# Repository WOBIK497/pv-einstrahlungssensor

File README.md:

# PV-Einstrahlungssensor

Ein kabelloser Sensor, der die Sonneneinstrahlung **in der Ebene einer PV-Fläche** misst – auch dann, wenn der Wechselrichter abregelt. Ein kleines Solarmodul arbeitet als Messzelle, ein zweites versorgt die Elektronik über einen Superkondensator. Die Werte gehen per [BTHome](https://bthome.io) an Home Assistant, ganz ohne Akku, Batterie oder Kabel.

> **Stand: Entwurf (November 2026).** Platine, Gehäuse und Programm sind fertig konstruiert und rechnerisch geprüft, aber **noch nicht gebaut**. Was am ersten Exemplar zu prüfen ist, steht unter [Offene Punkte](#offene-punkte). Nachbau auf eigenes Risiko.

**English summary:** A wireless, battery-free irradiance sensor for balcony/rooftop PV. A 70 mm ETFE solar cell operated near short circuit across a 10 Ω shunt measures plane-of-array irradiance; a second cell charges a 4 F supercapacitor. An Espruino-powered Raytac MDBT42Q (nRF52832) broadcasts the readings as BTHome v2, received by Home Assistant via Shelly Bluetooth proxies. Includes a scripted KiCad 9 PCB (38 × 46 mm, JLCPCB-ready), a parametric FreeCAD enclosure (black ASA, O-ring sealed, membrane vent, printed tab that bolts to the panel frame flush with its front edge) and the Espruino program. A section compares other radio links (Wi-Fi, Zigbee, 868 MHz GFSK and LoRa) for larger rooftop arrays without a Bluetooth receiver nearby. Documentation is in German.

---

## Inhalt

- [Wozu?](#wozu)
- [Funktionsprinzip](#funktionsprinzip)
- [Überblick](#überblick)
- [Elektronik](#elektronik)
- [Platine](#platine)
- [Gehäuse](#gehäuse)
- [Programm (Espruino)](#programm-espruino)
- [Home Assistant](#home-assistant)
- [Abgleich](#abgleich)
- [Einkaufsliste](#einkaufsliste)
- [Aufbau und Montage](#aufbau-und-montage)
- [Offene Punkte](#offene-punkte)
- [Warum so und nicht anders](#warum-so-und-nicht-anders)
- [Andere Funkwege](#andere-funkwege)
- [Ordnerstruktur](#ordnerstruktur)
- [Lizenz](#lizenz)

---

## Wozu?

Eine PV-Anlage mit Speicher regelt ab, sobald der Akku voll ist und im Haus wenig verbraucht wird. Ab dann zeigt die Leistung des Wechselrichters nur noch, was abgenommen wird, und nicht mehr, was die Sonne hergeben würde. Damit fehlt die Grundlage für alles, was auf die **mögliche** Leistung reagieren soll: Überschussladen, Prognosen abgleichen, Verschattung oder Verschmutzung erkennen.

Der Sensor misst diese Größe direkt. Weil er in derselben Ebene wie das Paneel sitzt, sieht er dieselbe Einstrahlung, also Sonnenstand, Neigung, Ausrichtung und Wolken genauso wie das große Modul.

Für die eigene Anlage sind **drei** Sensoren vorgesehen, je einer pro Fläche:

| Sensor  | Paneele | Azimut | Neigung zur Waagerechten |
|---------|---------|--------|--------------------------|
| Süd     | 1 und 2 | 180°   | 55°                      |
| Südwest | 4       | 236°   | 65°                      |
| West    | 3       | 260°   | 65°                      |

Ein einziger Sensor und eine Umrechnung über die Geometrie hätten nicht genügt: Paneel 3 und 4 sind gleich steil, zeigen aber 24° auseinander, und das Verhältnis ihrer Erträge schwankte im Herbst zwischen 1,2 und 3,2.

## Funktionsprinzip

Eine Solarzelle liefert im Kurzschluss einen Strom, der sehr genau proportional zur Einstrahlung ist. Die Spannung hängt dagegen kaum davon ab. Der Sensor lässt das Messmodul deshalb fast im Kurzschluss auf einen 10-Ω-Widerstand (Shunt) arbeiten und misst die Spannung daran:

- 0,8-W-Modul, Kurzschlussstrom 143 mA bei 1.000 W/m²
- 143 mA × 10 Ω = **1,43 V bei 1.000 W/m²**, also rund **699 W/m² pro Volt**
- Selbst bei 1.300 W/m² (Sonne plus Reflexion von Wolkenrändern) sind es erst 1,86 V. Das ist ein Viertel der Leerlaufspannung, die Zelle bleibt im linearen Bereich (Abweichung < 0,5 %).

Ein zweites, baugleiches Modul lädt einen Superkondensator, aus dem das Funkmodul lebt. Messung und Versorgung sind getrennt, damit der Ladestrom die Messung nicht verfälscht.

## Überblick

| | |
|---|---|
| Messgröße | Einstrahlung in der Modulebene, W/m² |
| Messzelle | ETFE-Solarmodul 70 × 70 mm, 0,8 W, auf 10-Ω-Shunt |
| Versorgung | zweites Modul → 5-V-Regler → Superkondensator 5,5 V / 4 F → 3,3 V |
| Funk | BTHome v2 (Bluetooth LE Advertising), unverschlüsselt |
| Funkmodul | Raytac MDBT42Q-512KV2 (nRF52832), Espruino selbst per SWD aufgespielt |
| Takt | messen alle 3 s, senden jede Sekunde |
| Verbrauch | ≈ 40 µA im Mittel, Kondensator überbrückt ≈ 2 Tage Dunkelheit |
| Kaltstart | ≈ 6 min bei bedecktem Himmel (200 W/m²) |
| Platine | 38 × 46 mm, 2 Lagen, SMD-Bestückung durch JLCPCB |
| Gehäuse | 3D-Druck (ASA, schwarz), 160 × 90 × 32,2 mm, O-Ring-gedichtet, Druckausgleichselement, angedruckte Lasche für den Paneelrahmen |
| Kosten | rund 90 € für einen Sensor, jeder weitere rund 50 € |

## Elektronik

```
VERSORGUNG
  Modul V (J1) ─ R2 10 Ω ─ U1 HT7550 (5,0 V) ─ D1 B5819WS ─┬─ VCAP ≤ 4,8 V ── J3: Superkondensator 4 F / 5,5 V
                C1 10 µF        C2 10 µF                 │   C3, C4 2 × 22 µF
                                                         ├─ R4 1 MΩ ─┬─ R5 1 MΩ ─ GND
                                                         │           └─ DIV → P0.30 (D30), C9 100 nF
                                                         └─ U2 XC6206 (3,3 V) ─ 3V3 → MDBT42Q
                                                               C6 10 µF, C7 100 nF
MESSUNG
  Modul M (J2) ─┬─ R1 10 Ω, 2 W (Shunt) ─ GND
                └─ R3 10 kΩ ─ SENSE 0 … 1,9 V → P0.31 (D31), C8 100 nF

MDBT42Q (U3):  P0.00 (D0) Taster-Ersatz J5 · P0.01 (D1) LED D2 über R6 1 kΩ
               RX mit R7 1 MΩ nach GND · SWD, RX, TX auf J4
```

- **R2** vor dem 5-V-Regler nimmt dem kleinen SOT-23-Gehäuse bei vollem Ladestrom die Wärme ab (sonst bis zu 0,2 W im Regler).
- **D1** verhindert, dass sich der Kondensator nachts über Regler und Modul entlädt.
- **R4/R5** teilen die Kondensatorspannung durch zwei (Querstrom 2,4 µA).
- **R7** hält RX auf Masse, damit Espruino beim Start nicht versehentlich die serielle Konsole statt Bluetooth wählt.
- Taster und LED liegen wie auf dem offiziellen Espruino-Breakout an D0 und D1, Programme und Anleitungen dafür passen also unverändert.
- Ruhestrom beider Regler zusammen ≈ 3 µA (HT7550 1,5 µA, XC6206 1 µA).

**Anschlüsse** (eckiges Pad = Pin 1, bei J1–J3 also Plus):

| | Belegung | Wofür |
|---|---|---|
| J1 | + / −, ZH-Buchse 1,5 mm | Modul V (Versorgung), Stecker des Moduls direkt |
| J2 | + / −, ZH-Buchse 1,5 mm | Modul M (Messung), Stecker des Moduls direkt |
| J3 | + / −, ZH-Buchse 1,5 mm | Superkondensator über ein konfektioniertes ZH-Kabel |
| J4 | GND, 3V3, SWDIO, SWDCLK, RX, TX | Espruino aufspielen (SWD); im Notfall serielle Konsole |
| J5 | D0 / 3V3 | Taster-Ersatz: beim Einschalten überbrücken, um gespeicherten Code zu umgehen |

J4 und J5 sind Lötaugen im Raster 2,54 mm.

## Platine

| Oberseite | Unterseite |
|---|---|
|  |  |

Zwei Lagen, 38 × 46 mm, alle Bauteile oben. Die Antenne des Funkmoduls sitzt an der Oberkante, darunter bleibt ein 4 mm breiter Streifen auf beiden Lagen kupferfrei. Links die Messung, unten die Versorgung, rechts die Programmierleiste. Die Unterseite ist eine durchgehende Massefläche. Die Entwurfsregelprüfung (DRC) von KiCad meldet **0 Fehler und 0 offene Verbindungen** (`drc.json`).

Die Platine wird vollständig per Skript erzeugt. Es gibt keinen Schaltplan in KiCad, die Netze stehen in `erzeuge_platine.py`.

```bash
cd Einstrahlungssensor-Platine
./erzeuge_fertigung.sh     # baut die Platine, DRC, Gerber-ZIP, BOM/CPL, Renderings
```

Voraussetzung: KiCad 9 mit Python-Modul `pcbnew` und `kicad-cli` (getestet mit 9.0.8 unter Kubuntu).

> Falle beim Skripten: Der Zonen-Füller stürzt auf einem frisch erzeugten `BOARD` ab. Das Skript speichert deshalb erst, lädt neu und füllt dann.

### Bestellen bei JLCPCB

1. `einstrahlungssensor-gerber.zip` hochladen. Die Vorgaben passen: 2 Lagen, 1,6 mm. Als Oberfläche **LeadFree HASL** statt OSP wählen, weil Funkmodul und Buchsen nach dem Reflow noch von Hand gelötet werden.
2. „PCB Assembly“ einschalten: Economic, Seite „Top“, bis zu 5 Platinen bestücken, **Confirm Parts Placement = Yes**.
3. `jlcpcb-bom.csv` und `jlcpcb-cpl.csv` hochladen (11 Positionen). Alle Teile haben LCSC-Nummern. J1–J5 und das Funkmodul fehlen mit Absicht.
4. **In der Bestückungsvorschau prüfen:** Polung von D1 (Kathodenstrich zu J3/C3) und D2, Lage von U1 (Pin 1 links oben) und U2 (Pin 1 rechts unten). JLCPCB dreht manche Bauteile anders als KiCad; die CPL enthält dafür schon eine Drehkorrektur. Nach der Bestellung die Platzierung binnen 72 Stunden freigeben.
5. Die ZH-Buchsen J1–J3 sind Durchsteckteile und stehen nicht in der Stückliste. Du lötest sie selbst ein und kaufst sie getrennt: JLCPCB verschickt keine losen Teile, was dort zusätzlich gekauft wird, bleibt im Teilelager für spätere Bestückungen.

Bei der Bestellung (November 2026) fielen außerdem auf: JLCPCB setzt mit der Voreinstellung „Tooling holes: Added by JLCPCB“ zwei Werkzeuglöcher (Ø 1,15 mm, nicht durchkontaktiert) in die oberen Ecken. Sie liegen im kupferfreien Antennenstreifen und außerhalb der Schlitzhalter im Gehäuse und stören nicht. In die EU zieht der Versand „Global Standard Direct Line“ Einfuhrumsatzsteuer, EU-Zoll und EU-Bearbeitungsgebühr gleich mit ein; bei den Express-Diensten unter IOSS kommen Zoll und Gebühr erst bei der Zustellung dazu.

| Bauteil | LCSC | Hinweis |
|---|---|---|
| HT7550-1 (MSKSEMI), 5-V-Regler | C5379082 | Pin 1 GND, 2 VIN, 3 VOUT |
| XC6206P332MR, 3,3-V-Regler | C5446 | Pin 1 GND, 2 VOUT, 3 VIN (anders als der HT7550!) |
| 10 Ω, 1 %, 2 W, 2512 (R1, R2) | C414890 | |
| B5819WS Schottky (D1) | C7420331 | |
| ZH-Buchse 2-polig, stehend (J1–J3) | – | Bauform JST B2B-ZR, nicht in der Stückliste: getrennt kaufen und selbst einlöten |
| übrige R, C und LED | siehe BOM | Standardteile |

### Funkmodul und Buchsen auflöten

Die drei ZH-Buchsen J1–J3 von oben einstecken und von unten verlöten, das eckige Pad (Pin 1, Plus) beachten. Sie sind unkritisch, am besten nach dem Funkmodul, damit sie beim Löten des Moduls nicht im Weg sind.

Das MDBT42Q lötest du ebenfalls selbst auf (Pads im Abstand von 0,7 mm an der Kante):

1. Viel Flussmittel, feine Spitze, Entlötlitze für Brücken.
2. Eine Ecke heften, Lage prüfen, dann die gegenüberliegende Ecke, dann den Rest.
3. Antenne zur Oberkante, Pad 1 (Markierung) oben links.
4. Vor dem ersten Einschalten mit dem Multimeter prüfen, dass 3V3 und GND an J4 nicht kurzgeschlossen sind.

Ohne Lötkolben geht es auch mit einer **Heizplatte** und Niedertemperatur-Lötpaste (Sn42Bi58, schmilzt bei 138 °C): Paste mit der Nadel auf die Pads, Modul auflegen, Platte auf etwa 170–180 °C. Die Lötstellen der JLCPCB-Bestückung (bleifrei, 217 °C) schmelzen dabei nicht, nichts verrutscht. Vorher einen Probelauf mit etwas Paste machen, weil die Anzeige der Platte mehr zeigt, als oben auf der Platine ankommt. Erst danach die ZH-Buchsen und J4 mit dem Lötkolben einlöten, die Buchsengehäuse nicht mit auf die Platte. Wismut-Lot ist etwas spröder als normales; für ein Modul mit vielen Pads im geschlossenen Gehäuse ist das vertretbar.

## Gehäuse

| Unterteil | Boden |
|---|---|
|  |  |

Zwei Druckteile, beide passen auf ein 180-mm-Druckbett. Für ASA braucht der Drucker einen geschlossenen Bauraum (z. B. Prusa Core One):

- **Außenmaß** 160 × 90 × 32,2 mm (Unterteil 25,0 mm, Deckel 7,2 mm), mit Lasche 160 × 118 mm. Innenraum 149,6 × 79,6 × 22,6 mm.
- **Deckel:** eine gemeinsame Tasche (143,4 × 72,2 × 2,8 mm) für beide Module. Die Module liegen auf einer 1 mm dicken Klebefuge und schließen **bündig** mit der Deckeloberseite ab. Abstandsnoppen auf dem Klebering (vier je Modul) legen die Fugendicke fest, Positionsnoppen an den Taschenwänden die Lage, zwei Distanznoppen halten 1 mm Abstand zwischen den Modulen. Unter jedem Modul ein Fenster für Kabel und Anschlussdose. Obere Außenkante mit R 2 abgerundet, außer zur Rahmenseite.
- **Dichtung:** geschlossener **O-Ring 148 × 2 mm, EPDM 70** (wetter-, UV- und ozonfest) als Axialdichtung in einer Nut von 2,8 × 1,5 mm (≈ 25 % Verpressung, 75 % Nutfüllung, 1,9 % Dehnung). Passend sind O-Ringe mit 146–150 mm Innendurchmesser.
- **Verschraubung:** acht Senkschrauben **M3 × 30** von unten durch Dome im Unterteil in Gewindeeinsätze M3 × 5,7 im Deckel (5 mm Gewindeeingriff). Die Nut läuft innen um die Dome herum, die Schraubenlöcher liegen also außerhalb der Dichtung.
- **Druckausgleich:** ein Membranelement **M12 × 1,5** sitzt versenkt in einer Tasche im Boden (Sechskant gegen Mitdrehen), innen mit einer Gegenmutter gekontert. Es lässt Luft durch, aber kein Wasser, und verhindert, dass das Gehäuse bei Temperaturwechseln Feuchtigkeit ansaugt.
- **Platine:** Die Antennenkante steckt in zwei Haltern mit Schlitz, die Unterkante liegt auf zwei Abstandshaltern (5 mm) und wird mit zwei Linsenkopfschrauben M3 × 6 (ISO 7045) befestigt, die sich ihr Gewinde im 2,6-mm-Loch selbst formen.
- **Superkondensator:** liegt zwischen zwei Stirnanschlägen (an der Drahtseite niedrig, die Drähte laufen darüber) und wird in zwei Schnappklammern gedrückt (federnde Arme 1,0 mm dick, Rastnase 25° über dem Zellenäquator, 1,1 % Dehnung beim Einrasten – ASA ist spröder als PETG und quer zu den Lagen schwächer, darum unter 2 %).
- **Befestigung:** Die Halterung ist für **quer oder hochkant verbaute Paneele** gedacht. Bei quer verbauten (lange Seite waagerecht) liegen die Montagelöcher in den Rahmenseiten oben und unten, der beste Platz für den Sensor ist **oben**: Dort sieht er denselben Himmel wie das Paneel, wird nicht von Brüstung, Geländer oder einer unteren Paneelreihe verschattet, und Regenwasser, Schnee und Schmutz laufen vom Paneel nach unten ab statt über den Sensor. Bei hochkant verbauten sitzt der Sensor seitlich an einer Langkante, am besten am oberen Montageloch. Das Gehäuse sitzt neben der oberen Langkante des Paneels und liegt mit der Wand direkt am Rahmen an. Eine Lasche (160 × 28 × 2,2 mm), in einem Stück mit dem Unterteil gedruckt, greift hinten unter den Fußflansch des Rahmens und wird mit **einer M6-Schraube durch ein Montageloch im Rahmenflansch** gehalten (Langloch ±2 mm). Gemeint sind die Montagelöcher, die gerahmte PV-Paneele ab Werk im Fußflansch der langen Rahmenseiten haben und die im Datenblatt des Paneels eingezeichnet sind. Gebohrt wird nichts. So liegt der Deckel **bündig mit der Rahmenvorderkante**: Das Gehäuse verschattet das Paneel nicht und der Rahmen nicht die Module. Die Wand am Rahmen verhindert das Verdrehen und trägt das Gewicht. Zur Rahmenseite haben Unterteil und Deckel keine Eckradien, damit sich kein Schmutz in Zwickeln sammelt. Die Lasche ist nur 2,2 mm dick, weil sie genau den Höhenunterschied zwischen Gehäuse (32,2 mm) und Rahmen (30 mm) ausfüllt. Sie hält trotzdem rund 270 N senkrecht zum Paneel (ASA, vorsichtig mit 40 MPa gerechnet), eine Sturmböe drückt mit 15–20 N. Rahmenmaße nach dem Datenblatt JA Solar JAM60D41 (langer Rahmen 30 mm hoch, Fußflansch 28 mm, Lochmitte 19 mm von der Außenfläche): Bei anderen Paneelen die Parameter `RAHMEN_*` und `MONTAGELOCH_ABSTAND` im Skript anpassen.

| Montiert, von vorn | Montiert, von hinten |
|---|---|
|  |  |

Alle Maße stehen als Parameter oben in `erzeuge_gehaeuse.py`. Neu erzeugen (FreeCAD 1.x, headless):

```bash
cd Einstrahlungssensor-Gehäuse
freecad.cmd erzeuge_gehaeuse.py     # → gehaeuse-unterteil/-deckel als STL und STEP
freecad.cmd pruefe_gehaeuse.py      # Passungsprüfung: Platine, Stecker, Kondensator, Druckausgleich
python3 vorschau.py                 # Vorschaubilder in Bilder/ (nur Pillow nötig)
```

Das Skript gibt beim Bauen die wichtigsten Kontrollmaße aus: Gewindeeingriff, Wandstärken an Einsätzen und Senkungen, Nutfüllung, O-Ring-Dehnung, Federweg der Schnappklammern. `pruefe_gehaeuse.py` meldet für den aktuellen Stand **0 Überschneidungen**.

`live_ansicht.py`, `live_uebernehmen.sh` und `live_befehl.sh` sind ein Hilfsmittel zum gemeinsamen Konstruieren: Das Makro läuft in der FreeCAD-Oberfläche, baut das Modell neu, sobald sich das Skript ändert, und zeigt Platine, Kabel, Schrauben und Module mit. Die Texturen dafür liegen im Ordner `Live-Ansicht/`, der nicht im Repository ist. Die Moduloberfläche erzeugt `erzeuge_modultextur.py`, die Platinenbilder kommen von `platine_ansicht_daten.py`. Für den Nachbau braucht man das alles nicht.

Zum Anschauen gibt es die Baugruppe als FreeCAD-Datei: `Gehäuse mit Einbauteilen offen.FCStd` und `… geschlossen.FCStd` zeigen das Gehäuse mit allen Einbauteilen am Paneelrahmen; `Gehäuse mit Einbauteilen.FCStd` ist ein älterer Stand ohne Lasche und Gewindeeinsätze. In „offen“ und „geschlossen“ sind die Bilder von Solarmodulen, Platine, Funkmodul und Druckausgleich eingebettet. FreeCAD 1.1 zeichnet Bilder auf Part-Objekten aber nicht selbst, darum legt das Hilfsobjekt `Texturen` sie beim Öffnen auf. Dafür muss `pv_textur.py` für FreeCAD importierbar sein, z. B. als Verknüpfung in einem Unterordner von `Mod/` in den FreeCAD-Benutzerdaten (den Pfad nennt `App.getUserAppDataDir()`, beim Snap `~/snap/freecad/common/`). Ohne das Modul öffnen sich die Dateien trotzdem, die Bildflächen bleiben dann grau.

### Drucken

- **Material: ASA, schwarz.** Die beiden schwarzen Solarzellen im Deckel heizen sich in der Sommersonne auf 65–70 °C auf, und das Gehäuse liegt direkt am Rahmen des PV-Paneels, der ebenso heiß wird. PETG wird ab etwa 70 °C weich und gäbe unter der Dauerlast (O-Ring-Pressung durch acht Schrauben, gespannte Lasche) über die Jahre nach; ASA hält bis etwa 95 °C und ist dazu UV-beständig. Schwarz, weil Ruß als Pigment am wenigsten ausbleicht und zusätzlich UV abfängt; ein heller Kunststoff kühlt kaum, denn die Wärme kommt vor allem von den Modulen im Deckel. Kein PLA (weich ab etwa 55 °C). PETG geht auf einem offenen Drucker zur Not auch, hält aber weniger lange.
- **Drucker:** ASA nur mit geschlossenem Bauraum, auf einem offenen Drucker verzieht sich das 16 cm lange Unterteil. Brim am Unterteil, Bauraum vorheizen, Raum lüften (Styrol).
- **Lage:** Unterteil mit dem Boden aufs Bett, die Lasche liegt mit auf. Deckel mit der Tasche nach oben. Kein Stützmaterial. Die Klammerarme stehen senkrecht, ihre Biegung geht quer zu den Lagen – nicht anders drucken, aber auch nicht beim Einsetzen des Kondensators hebeln.
- **Einstellungen:** 0,2 mm Schichthöhe, 4 Perimeter, 5 obere und untere Schichten, 25 % Gyroid. Die vielen Perimeter machen die Wände dicht.
- **Gewindeeinsätze:** Löcher 4,0 mm für M3 × 5,7 im Deckel, passend etwa zu Ruthex. Andere Einsätze → Maße im Skript anpassen.

## Programm (Espruino)

[`Firmware/einstrahlung-sued.js`](Firmware/einstrahlung-sued.js) misst alle 3 Sekunden beide Spannungen (16-fach gemittelt) und sendet sie jede Sekunde als BTHome-Advertising:

| BTHome-Objekt | Wert | Auflösung |
|---|---|---|
| `0x0C` voltage | Spannung am Shunt | 1 mV ≙ 0,7 W/m² |
| `0x4A` voltage | Spannung am Superkondensator | 0,1 V |

Espruino misst relativ zur Betriebsspannung. Das Programm rechnet deshalb mit `E.getAnalogVRef()` in Volt zurück. Für die anderen Sensoren änderst du nur `NAME` in der ersten Zeile.

**Espruino einmalig aufspielen.** Das nackte MDBT42Q kommt vom Distributor ohne Firmware. Espruino kommt deshalb einmal per SWD über J4 darauf, als Programmer dient ein Raspberry Pi Pico mit der Firmware [debugprobe](https://github.com/raspberrypi/debugprobe) (UF2-Datei per Drag-and-drop):

1. Verdrahtung Pico → J4: GP2 → SWDCLK, GP3 → SWDIO, GND → GND. Solange der Superkondensator noch nicht eingesteckt ist, darf der Pico die Platine über 3V3 versorgen. Mit eingestecktem, geladenem Kondensator 3V3 **nicht** verbinden, sonst fließt Strom rückwärts durch den XC6206.
2. Neue nRF52 sind oft per APPROTECT gesperrt. Erst entsperren (löscht den Chip):
   `openocd -f interface/cmsis-dap.cfg -f target/nrf52.cfg -c "init; nrf52_recover; exit"`
3. Die `.hex`-Datei für das MDBT42Q von [espruino.com/Download](https://www.espruino.com/Download) aufspielen:
   `openocd -f interface/cmsis-dap.cfg -f target/nrf52.cfg -c "program <datei>.hex verify reset exit"`

Ein ST-Link reicht dafür nicht: Er kann einen gesperrten nRF52 nicht entsperren. Der Pico bringt mit debugprobe außerdem eine serielle Schnittstelle mit (GP4 → RX, GP5 ← TX an J4), für die Espruino-Konsole mit 9600 Bd. Wer Espruino auf fremder Hardware nutzt, freut sich das Projekt über eine Spende.

**Programm aufspielen** (per Bluetooth, auch wenn der Sensor schon montiert ist):

1. Die [Espruino Web IDE](https://www.espruino.com/ide/) in Chrome öffnen. Unter Linux vorher in `chrome://flags` die „Experimental Web Platform Features“ einschalten. Von Android geht es ohne diesen Schritt.
2. Kondensator laden lassen (oder kurz 3,3 V an J4 anlegen), mit dem Modul verbinden, Programm einfügen und hochladen.
3. In der Konsole `save()` eingeben. Danach startet das Programm nach jedem Stromausfall von selbst.

**Absichern:** Solange das Modul verbindbar ist, kann sich jeder in Funkreichweite mit der Web IDE verbinden. Mit `E.setPassword("…")` und `E.lockConsole()` lässt sich die Konsole sperren. Passwort vergessen: J5 beim Einschalten etwa 5 Sekunden überbrücken, dann startet das Modul ohne gespeichertes Programm.

## Home Assistant

Die **BTHome-Integration** erkennt den Sensor von selbst, sobald ein Bluetooth-Empfänger ihn hört (hier: Shelly-Geräte als Bluetooth-Proxy). Weil die Bibliothek die Werte nach Objektnummer sortiert, kommt die Shunt-Spannung zuerst. Die Entitäten heißen voraussichtlich „Spannung“ und „Spannung 2“.

Für die Einstrahlung einen **Template-Sensor** anlegen (Helfer → Template → Sensor):

- Einheit `W/m²`, Geräteklasse „Bestrahlungsstärke“ (`irradiance`), Zustandsklasse „Messung“
- Zustand:

```jinja
{{ (states('sensor.einstr_sued_spannung') | float(0) * 699) | round(0) }}
```

Die Entitäts-ID durch die tatsächliche ersetzen, den Faktor 699 nach dem [Abgleich](#abgleich) durch den gemessenen.

**Recorder entlasten:** Die Shunt-Spannung ändert sich fast bei jeder Messung. Ein Sensor im 3-Sekunden-Takt erzeugt zusammen mit seinem W/m²-Sensor knapp 60.000 Zustände am Tag. Die rohen Spannungen deshalb vom Recorder ausschließen und nur die W/m²-Werte speichern:

```yaml
recorder:
  exclude:
    entity_globs:
      - sensor.einstr_*_spannung*
```

## Abgleich

Der Faktor 699 ist der Nennwert aus dem Datenblatt. Für den echten Wert an Tagen ohne Abregelung die Shunt-Spannung gegen die Leistung der zugehörigen Strings aufzeichnen und aus **5-Minuten-Mittelwerten bei klarem Himmel** den Faktor je Fläche bestimmen. Die Mittelung gleicht auch den Versatz von ein, zwei Sekunden zwischen Sensor und Wechselrichter aus. Bei mehreren Sensoren müssen diese untereinander nicht synchron senden, weil jeder nur mit seinen eigenen Strings verglichen wird.

Bei mehreren Sensoren sollten die **Messmodule aus derselben Charge** stammen, damit alle gleich messen. Bei den Versorgungsmodulen ist das egal.

## Einkaufsliste

Für einen Sensor, Preise vom November 2026 inklusive Mehrwertsteuer, ohne Versand:

| Teil | Menge | ca. Preis | Bezug |
|---|---|---|---|
| Funkmodul Raytac MDBT42Q-512KV2 (nRF52832, 512 KB, Keramikantenne), ohne Firmware | 1 | ≈ 6 € | z. B. [TME](https://www.tme.eu/de/details/mdbt42q-512kv2/iot-wifi-bluetooth-modules/raytac/); nicht das MDBT42Q-PAT (nRF52810, kein Espruino). Der Espruino-Shop hatte das nackte Modul im November 2026 nicht mehr, nur das Breakout, das nicht auf die Platine passt |
| Raspberry Pi Pico (H) als SWD-Programmer, einmalig für alle Sensoren | 1 | ≈ 5–10 € | |
| Leiterplatten, bestückt (JLCPCB fertigt mindestens 5) | 5 | ≈ 23 $ für alle fünf bestückt, mit Versand und Einfuhrabgaben nach Deutschland und Neukunden-Gutschein (November 2026) | JLCPCB |
| ZH-1,5-Set: 2-polige Stecker mit Kabel und stehende Platinenbuchsen (Buchsen für J1–J3, ein Kabel für J3) | 1 Packung | ≈ 8 € | z. B. Amazon (Nachbau, Passung zu den Modulsteckern prüfen) |
| ETFE-Solarmodul 0,8 W, 6 V, 70 × 70 × 2 mm, ZH-1,5-Stecker (1 × Messung, 1 × Versorgung) | 2 | 17–32 € | AliExpress |
| Superkondensator 5,5 V / 4 F (Kombityp, zwei Zellen) | 1 | 3,50 € | AliExpress |
| Druckausgleichselement M12 × 1,5, PA, PTFE-Membran, IP68 (z. B. Jacob JDAE12) | 1 | 3,25 € | Fachhandel |
| O-Ring 148 × 2 mm, EPDM 70 | 1 | 4 € | Fachhandel |
| Gewindeeinsätze M3 × 5,7 | 8 | | z. B. Ruthex |
| Befestigung: Sechskantschraube M6 × 16 (ISO 4017), Karosseriescheibe 6,4 × 18, Sicherungsmutter M6 (DIN 985), Edelstahl | je 1 | | |
| Senkschrauben M3 × 30 (ISO 10642), Edelstahl | 8 | | |
| Linsenkopfschrauben M3 × 6 (ISO 7045), Edelstahl, für die Platine | 2 | | |
| Mutter M12 × 1,5 (Kunststoff), falls beim Druckausgleich keine dabei ist | 1 | | |
| ASA, schwarz | ≈ 100 g | | |

Wer mehrere Sensoren baut, braucht alles außer den Leiterplatten und dem ZH-Set entsprechend öfter. Pro weiterem Sensor kommen so rund 50 € dazu. Die Messmodule sollten dann aus derselben Charge stammen (siehe [Abgleich](#abgleich)).

Dazu aus der Bastelkiste: Lötzinn, Flussmittel, Entlötlitze, Schrumpfschlauch, wetterfester Kleb- und Dichtstoff auf MS-Polymer-Basis für die Module. Eine 6-polige Stiftleiste für J4 (zum Aufspielen von Espruino) und ein paar Jumperkabel Buchse–Buchse.

## Aufbau und Montage

1. Funkmodul und die drei Buchsen auf die bestückte Platine löten und auf Kurzschluss prüfen (siehe [oben](#funkmodul-und-buchsen-auflöten)).
2. Gewindeeinsätze einschmelzen: acht M3 von unten in den Deckel.
3. Druckausgleichselement von außen in die Bodentasche setzen und innen mit der Mutter kontern.
4. Dichtstoff auf den Klebering geben, die Kabel der Solarmodule durch die Fenster im Deckel fädeln und die Module in die Tasche drücken, bis sie auf den Abstandsnoppen aufliegen und zwischen den Positionsnoppen sitzen. Das Messmodul markieren.
5. Die Fugen um die Module umlaufend mit dem Kleber versiegeln. Die Module sind auf FR-4 laminiert, die offene Kante ist die Schwachstelle.
6. **Polung der Modulstecker prüfen:** Rot (Plus) muss auf die Seite mit dem „+“ auf der Platine. Falls nicht, lassen sich die Kontakte aus dem ZH-Gehäuse lösen und tauschen (Lasche mit einer Nadel anheben). Verpolt geht nichts kaputt, der Sensor misst und lädt dann nur nicht.
7. Messmodul in J2, Versorgungsmodul in J1. Ein ZH-Kabel an den Superkondensator löten (Rot an Plus, Schrumpfschlauch) und in J3 stecken. Alternativ den Kondensator direkt auf die Platine löten: J3 dann nicht bestücken und die Kondensatordrähte, falls nötig mit zwei Litzen verlängert, in die Lötaugen von J3 löten, Plus ans eckige Pad. Der Kondensator lässt sich dann allerdings nicht mehr abziehen.
8. Platine mit der Antennenkante schräg in die Schlitze schieben, ablegen, unten mit zwei M3 × 6 festschrauben. Kondensator in die Klammern drücken.
9. O-Ring in die Nut legen, Deckel aufsetzen und mit acht M3 × 30 von unten gleichmäßig anziehen, bis er rundum aufliegt.
10. Den Sensor an die obere Langkante des quer verbauten Paneels setzen (bei hochkant verbauten seitlich ans obere Montageloch): Wand am Rahmen, Lasche hinten am Fußflansch, Langloch über dem Montageloch im Rahmenflansch. Die M6 × 16 von innen durch den Flansch stecken (Kopf zwischen Flansch und Paneel), hinten Karosseriescheibe und Sicherungsmutter, nur mäßig anziehen – auch ASA gibt unter zu viel Druck auf Dauer nach. Nicht in den Rahmen bohren.

## Offene Punkte

Folgendes ist bisher nur aus Datenblättern und Quelltext abgeleitet. Deshalb zuerst **ein** Exemplar bauen und in Betrieb nehmen:

- **Bestückung:** Sitzen D1 und D2 richtig herum? Höchstens 4,9 V am Kondensator, 3,3 V an J4?
- **Stecker:** Passen die Modulstecker in die ZH-Buchsen, und auf welcher Seite liegt Rot?
- **Gehäuse:** Module (70,2 × 70,2 × 1,8 mm) und Kondensator (22,8 × 25,6 × 13,0 mm) sind nachgemessen und eingetragen, ebenso das Druckausgleichselement (Sechskantkopf SW 16,8 × 8,2 mm, Gewinde 10 mm, Belüftungsschlitze in der Kopfmitte frei vom 3 mm tiefen Sechskantsitz). Gegenmutter gemessen (5,1 mm hoch), der O-Ring des Elements liegt in einer Nut im Kopf. Der Grund dieser Tasche wird als Brücke gedruckt: Liegt der Dichtring des Elements dort sauber an? Bleibt das Gehäuse unter der Brause dicht?
- **Befestigung:** Passt das Paneel zum Datenblatt JAM60D41 (Rahmen 30 mm hoch, Flansch 28 mm), trifft das Langloch das Montageloch, liegt der Deckel bündig? Die Flanschdicke ist aus der maßstabsgetreuen Profilzeichnung im Datenblatt ausgemessen (≈ 1,7 mm), M6 × 16 reicht bis etwa 4 mm.
- **Empfang:** Hört ein Bluetooth-Proxy den Sensor am Montageort zuverlässig?
- **Nacht:** Wie weit sinkt die Kondensatorspannung bis zum Morgen (Leckstrom)?
- **Web Bluetooth:** Klappt die Verbindung vom Linux-Rechner oder nur vom Android-Gerät?
- **Home Assistant:** Welche Spannung landet unter welcher Entität?
- **Abgleich:** Faktor je Fläche aus Messungen bestimmen.

## Warum so und nicht anders

- **Espruino statt ESPHome:** ESPHome kann BTHome nur empfangen, nicht senden. Der Vorschlag, das Senden einzubauen ([esphome/esphome#14472](https://github.com/esphome/esphome/pull/14472)), wurde im Oktober 2026 ohne Übernahme geschlossen. Espruino bringt eine fertige [BTHome-Bibliothek](https://www.espruino.com/BTHome) mit, das Programm ist ein paar Zeilen JavaScript und lässt sich per Bluetooth ändern.
- **Eigene Platine statt Breakout auf Lochraster:** kleiner, robuster und kaum teurer, weil JLCPCB alles außer dem Funkmodul und den Buchsen bestückt.
- **Superkondensator statt Akku:** keine Alterung durch Ladezyklen, kein Problem mit Frost oder Hitze unter dem Modul.
- **Variante mit externer Stromversorgung:** Liegt am Montageort Strom an, wäre nur ein Modul nötig, nämlich das Messmodul. Versorgungsmodul, 5-V-Regler und Superkondensator entfallen, und das Gehäuse wäre nur halb so groß. Dadurch wäre auch WLAN (z. B. mit ESPHome) oder Zigbee2MQTT möglich, weil der höhere Stromverbrauch dann keine Rolle spielt (siehe [Andere Funkwege](#andere-funkwege)).
- **Verworfen:** Lux-Sensoren (enden bei etwa 83.000 lx und messen Lux statt W/m²), Industrie-Einstrahlungssensoren (450–700 € pro Stück). Ein Silizium-Pyranometer mit RS485 (z. B. PYR20, ca. 60 €) wäre die fertige Alternative, braucht aber Kabel. Fertige BTHome-Geräte mit freiem Analogeingang gibt es meines Wissens nicht.

## Andere Funkwege

Dieser Sensor bleibt bei Bluetooth LE, weil am Balkon Shelly-Geräte als Empfänger in Reichweite sind. Bei größeren Dachanlagen ist das oft nicht so. Die Übersicht ist für alle, die den Sensor dafür abwandeln wollen. Alle Zahlen sind Überschläge aus Datenblättern, gemessen ist davon nichts.

**Maßstab ist die Solarversorgung:** Das Versorgungsmodul liefert rund 0,14 mA je W/m², der Superkondensator gibt zwischen 4,7 und 2,0 V etwa 11 C ab. Damit er eine Winternacht von 15 Stunden überbrückt, darf der Sensor im Mittel höchstens etwa **0,2 mA** brauchen. Die Ströme unten beziehen sich auf den Kondensator. Der 3,3-V-Regler ist linear, es fließt also derselbe Strom hinein wie heraus.

**Reichweite und Verbrauch**

| Funkweg | Reichweite bei Sicht | Reichweite durchs Haus | Mittlerer Strom, ein Wert alle 3 s | Reicht die Solarversorgung? | Empfänger |
|---|---|---|---|---|---|
| Bluetooth LE (dieser Sensor) | 50–100 m | 10–20 m, ein bis zwei Wände | ≈ 40 µA | ja | Bluetooth-Proxy (Shelly, ESPHome) |
| Zigbee | 50–100 m je Sprung | 10–20 m je Sprung, das Mesh verlängert | ≈ 50–100 µA (Schätzung) | ja | Koordinator mit Zigbee2MQTT oder ZHA |
| WLAN | 50–100 m bis zum Zugangspunkt | 10–30 m | 20–80 mA, Spitzen über 300 mA | nein, nur mit Netzteil | keiner zusätzlich |
| 868 MHz GFSK | 0,5–1 km | 50–150 m, mehrere Wände oder Decken | ≈ 0,1 mA | ja | eigener Empfänger (ESP32 + Funkmodul) |
| 868 MHz LoRa | 2–5 km | einige hundert Meter | ≈ 0,8 mA | nur, wenn er nachts seltener sendet | eigener Empfänger oder LoRaWAN-Gateway |

Die Reichweiten sind Erfahrungswerte für kleine Antennen und gelten nur grob. Stahlbeton, metallbedampftes Wärmeschutzglas und der Alurahmen des Paneels verkürzen sie stark, ein hoch montierter Sensor mit freier Sicht verlängert sie.

**Vor- und Nachteile**

| Funkweg | Vorteile | Nachteile |
|---|---|---|
| Bluetooth LE | Geringster Verbrauch. Vorhandene Bluetooth-Proxys empfangen die Werte, Home Assistant erkennt BTHome von selbst. Das Programm lässt sich per Web Bluetooth ändern. | Kurze Reichweite, schon ein Ziegeldach kostet viel. Keine Empfangsbestätigung, verlorene Pakete fallen nur als Lücken auf. BLE Long Range (Coded PHY) beherrscht das nRF52832 nicht, und die üblichen Proxys hören es auch nicht. Ausweg ohne Umbau: ein ESP32 mit ESPHome und LAN-Anschluss als Proxy nahe der Anlage, z. B. auf dem Dachboden. |
| Zigbee | Mesh: Jedes netzbetriebene Zigbee-Gerät (Zwischensteckdose, Unterputzaktor) leitet weiter. Empfangsbestätigung und Wiederholung sind eingebaut. Als schlafendes Endgerät braucht der Sensor etwa so viel wie mit BLE. | Anderer Funkchip nötig (z. B. nRF52840, EFR32MG, ESP32-C6 oder -H2), das nRF52832 und Espruino können kein Zigbee. Ein selbst gebautes Gerät mit Analogwerten braucht in Zigbee2MQTT meist einen eigenen Converter. Je Sprung reicht es auf 2,4 GHz kaum weiter als BLE. |
| WLAN | Kein zusätzlicher Empfänger, wenn das WLAN bis zur Anlage reicht. Mit ESPHome direkt in Home Assistant, Updates über das Netz. | Den Strom schaffen weder das Versorgungsmodul noch der 3,3-V-Regler (XC6206, höchstens 200 mA). Ohne Netzteil nur mit Tiefschlaf, größerem Kondensator und stärkerem Regler, dann aber nur alle paar Minuten ein Wert. Auf dem Dach ist oft kein WLAN. |
| 868 MHz GFSK | Rund zehnmal so weit wie BLE bei kaum höherem Verbrauch: Ein Paket dauert bei 50 kbit/s etwa 4 ms und kostet ≈ 0,2 mC. Der 3-s-Takt hält auch nachts durch. Mit 0,13 % Sendezeit passt er in jeden Teilbereich des Bands. | Kein Standardprotokoll, Paketformat und Auswertung im Empfänger legt man selbst fest. Zusätzliches Funkmodul und eigener Empfänger. |
| 868 MHz LoRa | Größte Reichweite, durchs Haus problemlos. Mit LoRaWAN über The Things Network ginge es ohne eigenen Empfänger, wenn ein Gateway in Reichweite ist. | Ein Paket dauert bei SF7 etwa 50 ms und kostet ≈ 2,3 mC, rund hundertmal so viel wie bei BLE. Nachts wäre der Kondensator nach knapp 4 Stunden leer, bei Dunkelheit (Shunt-Spannung nahe 0) also z. B. nur alle 10 Minuten senden. Der 3-s-Takt (1,7 % Sendezeit) ist nur im Bereich 869,40–869,65 MHz erlaubt. The Things Network erlaubt 30 s Sendezeit pro Tag, bei SF7 also etwa einen Wert alle drei Minuten. |

### 868 MHz: Was GFSK und LoRa gemeinsam haben

Beide nutzen das europäische Band für Kurzstreckenfunk (863–870 MHz). Das durchdringt Wände und Dächer besser als 2,4 GHz, und die Empfänger sind deutlich empfindlicher. Für beide gilt:

- **Hardware:** ein Funkmodul mit SX1262 (z. B. Ebyte E22-900M22S, 14 × 20 mm) an SPI neben dem MDBT42Q. Bluetooth bleibt dann zum Programmieren erhalten. Einen fertigen Espruino-Treiber gibt es meines Wissens nur für den älteren SX127x (z. B. RFM95), für den SX1262 müsste man ihn selbst schreiben. Die Platine wird größer.
- **Strom:** ≈ 45 mA beim Senden mit +14 dBm, im Schlaf unter 1 µA. Die Spitzen liefert der Superkondensator, der XC6206 schafft sie.
- **Antenne:** Eine λ/4-Antenne ist etwa 8,6 cm lang. Eine Wendelantenne passt ins Gehäuse, ASA lässt die Funkwellen durch. Der Alurahmen direkt daneben verstimmt sie, das ist am Montageort zu prüfen. Eine Antenne außen wäre ein weiterer Durchbruch durch die Dichtung.
- **Empfänger:** ein eigenes Gerät, z. B. ein ESP32-Board mit SX1262 (rund 20 €) mit ESPHome, das die Pakete auswertet und an Home Assistant weitergibt. Die automatische Erkennung wie bei BTHome entfällt.
- **Funkregeln** (ETSI EN 300 220): Im Bereich 868,0–868,6 MHz darf ein Gerät höchstens 1 % der Zeit senden, im Bereich 869,40–869,65 MHz höchstens 10 %.

**Fazit:** Für eine Dachanlage ohne Bluetooth-Empfänger in der Nähe ist **GFSK auf 868 MHz** der beste Kompromiss: deutlich mehr Reichweite bei kaum höherem Verbrauch, der 3-s-Takt bleibt. LoRa lohnt erst bei wirklich langen Strecken. Liegt an der Anlage ohnehin Strom an, sind ein Bluetooth-Proxy in der Nähe oder WLAN mit Netzteil am einfachsten.

## Ordnerstruktur

```
├── Einstrahlungssensor-Platine/
│   ├── erzeuge_platine.py          Platine per KiCad-Python-API
│   ├── erzeuge_fertigung.sh        Neubau, DRC, Gerber, BOM/CPL, Renderings
│   ├── einstrahlungssensor.kicad_pcb / .kicad_pro
│   ├── einstrahlungssensor-gerber.zip, Gerber/
│   ├── jlcpcb-bom.csv, jlcpcb-cpl.csv
│   ├── drc.json                    Ergebnis der Entwurfsregelprüfung
│   └── Bilder/
├── Einstrahlungssensor-Gehäuse/
│   ├── erzeuge_gehaeuse.py         parametrisches Gehäuse (FreeCAD)
│   ├── gehaeuse-unterteil.stl/.step, gehaeuse-deckel.stl/.step
│   ├── pruefe_gehaeuse.py          Passungsprüfung
│   ├── vorschau.py                 Vorschaubilder ohne OpenGL
│   ├── beschrifte_montagebild.py   Pfeil und Text ins Montagebild
│   ├── Gehäuse mit Einbauteilen offen/geschlossen.FCStd   Baugruppe zum Anschauen
│   ├── pv_textur.py                legt die Bildflächen der Baugruppe beim Öffnen auf
│   ├── live_ansicht.py, live_uebernehmen.sh, live_befehl.sh,
│   │   platine_ansicht_daten.py, erzeuge_modultextur.py   Live-Ansicht (optional)
│   └── Bilder/
├── Firmware/
│   └── einstrahlung-sued.js        Espruino-Programm
├── LICENSE-CERN-OHL-S-2.0.txt
└── LICENSE-MIT.txt
```

## Lizenz

- **Hardware** (Platine, Gehäuse, Fertigungsdaten, Bilder): [CERN-OHL-S-2.0](LICENSE-CERN-OHL-S-2.0.txt). Wer veränderte Fassungen weitergibt oder daraus gebaute Geräte vertreibt, muss die geänderten Quelldaten unter derselben Lizenz offenlegen.
- **Software** (Python- und Shell-Skripte, Espruino-Programm): [MIT](LICENSE-MIT.txt).

Keine Gewähr. Der Sensor hängt im Freien an einer PV-Anlage. Montage und Betrieb erfolgen auf eigene Verantwortung.

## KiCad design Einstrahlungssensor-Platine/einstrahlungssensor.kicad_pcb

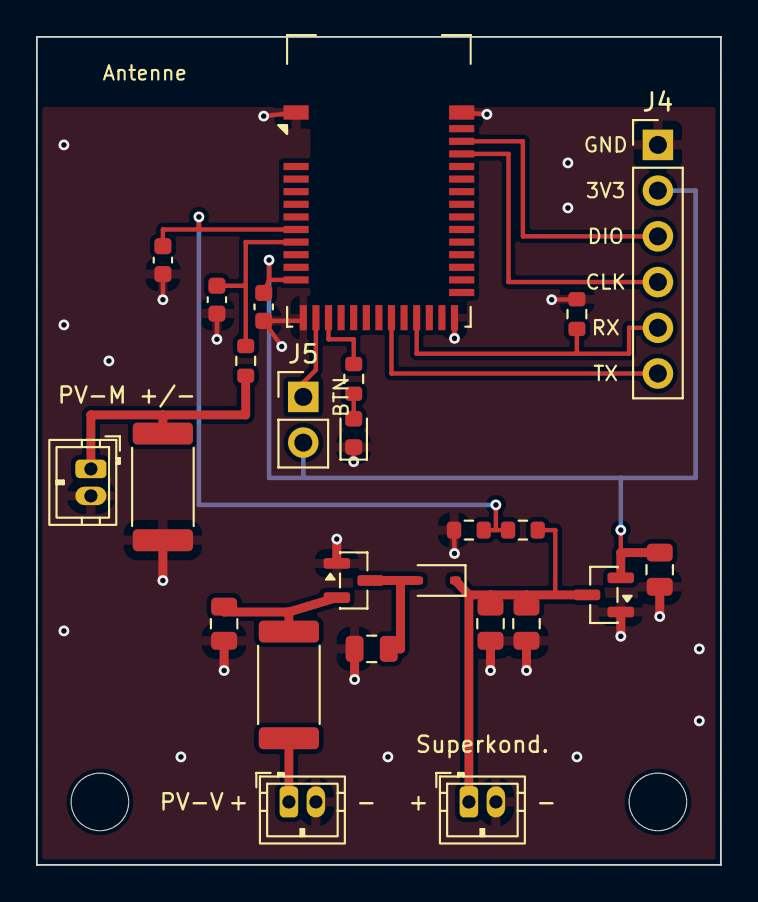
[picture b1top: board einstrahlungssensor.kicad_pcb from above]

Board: 2 copper layers, 38.0 x 46.0 mm, 27 parts (0 on the bottom side), 16 nets.

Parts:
C1, C2, C6: 10uF 25V; C_0805_2012Metric
C3, C4: 22uF 25V; C_0805_2012Metric
C7, C8, C9: 100nF; C_0603_1608Metric
D1: B5819WS; D_SOD-323
D2: LED rot; LED_0603_1608Metric
H1, H2: M3; MountingHole_3.2mm_M3
J1, J2, J3: HC-ZH1.5-2A; JST_ZH_B2B-ZR_1x02_P1.50mm_Vertical
J4: Debug; PinHeader_1x06_P2.54mm_Vertical
J5: BTN; PinHeader_1x02_P2.54mm_Vertical
R1, R2: 10R 1% 2W; R_2512_6332Metric
R3: 10k; R_0603_1608Metric
R4, R5, R7: 1M; R_0603_1608Metric
R6: 1k; R_0603_1608Metric
U1: HT7550-1; SOT-23
U2: XC6206P332MR; SOT-23
U3: MDBT42Q (Espruino); Raytac_MDBT42Q

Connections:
+3V3: C6.2, C7.2, J4.2, J5.2, U2.2, U3.11
+5V: C2.2, D1.2, U1.3
BTN: J5.1, U3.13
DIV: C9.2, R4.1, R5.2, U3.7
GND: C1.1, C2.1, C3.1, C4.1, C6.1, C7.1, C8.1, C9.1, D2.1, J1.2, J2.2, J3.2, J4.1, R1.1, R5.1, R7.2, U1.1, U2.1, U3.1, U3.12, U3.24, U3.39
LEDA: D2.2, R6.1
LEDSIG: R6.2, U3.14
PV_M: J2.1, R1.2, R3.1
PV_R: C1.2, R2.2, U1.2
PV_V: J1.1, R2.1
RX: J4.5, R7.1, U3.21
SENSE: C8.2, R3.2, U3.8
SWDCLK: J4.4, U3.36
SWDIO: J4.3, U3.37
TX: J4.6, U3.19
VCAP: C3.2, C4.2, D1.1, J3.1, R4.2, U2.3

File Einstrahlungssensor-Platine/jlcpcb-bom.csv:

Comment,Designator,Footprint,LCSC Part #
10uF 25V,"C1,C2,C6",C_0805_2012Metric,C15850
22uF 25V,"C3,C4",C_0805_2012Metric,C45783
100nF,"C7,C8,C9",C_0603_1608Metric,C14663
B5819WS,D1,D_SOD-323,C7420331
LED rot,D2,LED_0603_1608Metric,C2286
10R 1% 2W,"R1,R2",R_2512_6332Metric,C414890
10k,R3,R_0603_1608Metric,C25804
1M,"R4,R5,R7",R_0603_1608Metric,C22935
1k,R6,R_0603_1608Metric,C21190
HT7550-1,U1,SOT-23,C5379082
XC6206P332MR,U2,SOT-23,C5446
